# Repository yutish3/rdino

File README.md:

# Rdino - 2040
rp-2040 development board in the shape of arduino uno r3 so it supports its hats and also has esp32 for wifi and bluetooth and 5x5 grid of neo pixel leds

## VISION
main goals I had was making it is that I wanted to have a powerful board on which Arduino hats can fit with wireless capabilities so I used both rp 2040 and esp 32 and connected gpios of both so rp 2040 can off load some tasks to esp 32. so in a sense it is like Arduino UNO but on steroids 

and for usage too it can be used like a normal Arduino UNO 

it has dual microcontroller so all the less important repetative tasks can be off loaded to esp32 and main work can be done by the rp 2040 chip with extra 16M bit memory
and it can be used foor any project like lfr robot , micromouse , rc car etc

## what makes it special (main components)
&#9679; RP2040 :- main microcontroller

&#9679; W25Q128JVS :- 128Mbit Flash Memory for extra juice

&#9679; ESP32-C3-WROOM-02 :- backup microcontroller with wifi and Bluetooth capabilities 

&#9679; 25 X WS2812B-2020 :- programmable rgb leds

## Images

| Component | Purpose | Qty | Cost (INR) | Distributor |
| --- | --- | --- | --- | --- |
| RP2040 (QFN-56) | Main Microcontroller | 1 | ₹81.00 | [Evelta](https://evelta.com/rp2040-264kb-sram-dual-arm-cortex-m0-processor-mcu-by-raspberry-pi/?srsltid=AfmBOopaIG6fpnSNGs3z4S0e6P0bgP9_VYOyHm1yW1iu5uU8jt_uu5J_) |
| ESP32-C3-WROOM-02 | Wi-Fi / BLE Module | 1 | ₹312 | [Evelta](https://evelta.com/esp32-c3-wroom-02-n4-wi-fi-ble-module-4mb-flash-pcb-antenna/?sku=136-ESP32-C3-WROOM-02-N4&utm_source=google&utm_campaign=19958243666&utm_medium=cpc&utm_content=&utm_term=&gad_source=1&gad_campaignid=19958265965&gclid=Cj0KCQjwsMLSBhD9ARIsAIpUTDqEPgMN1OtKYFDDmMqUSGKSXAjHzA4DRwzgzZp3zSiW1o8-RgKeGbgaAoSMEALw_wcB) |
| W25Q128JVS (SOIC-8) | 128Mbit Flash Memory | 1 | ₹223 | [Evelta](https://evelta.com/serial-nor-flash-memory-128mbit-8pin-soic/?sku=153-W25Q128JVSIQ&utm_source=google&utm_campaign=19958243666&utm_medium=cpc&utm_content=&utm_term=&gad_source=1&gad_campaignid=19958265965&gclid=Cj0KCQjwsMLSBhD9ARIsAIpUTDqgAe2PFV_ZbwzCVTig-jSF6n-lNv5TzVO5kI0fkOoLNDz-UcC87KoaAvCyEALw_wcB) |
| AP2112K-3.3 (SOT-23-5) | 3.3V LDO Voltage Regulator | 1 | ₹24 | [Evelta](https://evelta.com/linear-voltage-regulator-positive-fixed-1-output-300ma-ic-sot-23-5/?sku=035-TLV74033PDBVR&utm_source=google&utm_campaign=19958243666&utm_medium=cpc&utm_content=&utm_term=&gad_source=1&gad_campaignid=19958265965&gclid=Cj0KCQjwsMLSBhD9ARIsAIpUTDpVNRkkdR8DkeeqQDI-B0SV4mmE5r7KHuDlczT8pWqQnIAxcDNvTTQaAnOdEALw_wcB#productDescription) |
| WS2812B-2020 (PLCC4) | Addressable RGB LEDs (D1-D24, D27, D29, D31) | 25 | ₹275 | [Robu](https://robu.in/product/1-month-warranty-953/?gad_source=1&gad_campaignid=17427802703&gclid=Cj0KCQjwsMLSBhD9ARIsAIpUTDpt1pzF430Rd8rggMbqOhyDVxqaDctheh1CFh1cCbUzKa_cTqI4nuYaAhGvEALw_wcB) |
| 74AHCT125 | 3.3v to 5v converter | 1 | ₹113 | [Lioncircuit](https://www.lioncircuits.com/parts/74AHCT125PW%2C118) |
| Standard LED (0603) | Status Indicator (D26) | 1 | ₹3.3 | [evelta](https://evelta.com/0603-orange-chip-led/?srsltid=AfmBOopJK48IT0WFYCzFETDcCPIIkiPRop17X2j5vajIVfQTBZ31vxPa) |
| USB-C Receptacle 14-Pin | Power and Data Interface (J1) | 1 | ₹8 | [Hubtronics](https://hubtronics.in/usb-type-c-16p-female-connector-surface-mount?srsltid=AfmBOordf7MpBH0Qx-t9NQyY5B-fdjtzOuCBNZ2MHx8Cz8tkCzKM3Jp4zG4) |
| 1x04 Pin Header/Socket | I/O Expansion / Programming (J6) | 1 | ₹11 | [Robu](https://robu.in/product/fh2-0-09-04pzd-xunpu-plugin1x4-pin-2mm-female-headers-rohs/?gad_source=1&gad_campaignid=17427802703&gclid=CjwKCAjw08fSBhA7EiwAfbQTsMGuGFKjKxeAs85tsGpJZ_VgBg9C0syUiuKSdEVnRGq6vaZT8pyhIhoCEKcQAvD_BwE)|
| 1x06 Pin Header/Socket | I/O Expansion (J2) | 5 | ₹53 | [Robu](https://robu.in/product/6-pin-female-11mm-tall-stackable-header-connector-for-arduino-5pcs/) |
| 1x08 Pin Header/Socket | I/O Expansion (J4, J5) | 2 | ₹32 | [Robu](https://robu.in/product/fh1-27-01-08pzd-xunpu-plugin1x8-pin-1-27mm-female-headers-rohs/?gad_source=1&gad_campaignid=17427802703&gclid=CjwKCAjw08fSBhA7EiwAfbQTsAXYrqE1Rld57TzQKy9yslqVRvfkEbmGVCeCCZim9T4gCUaC_6xX4xoCpCAQAvD_BwE) |
| 1x10 Pin Header/Socket | I/O Expansion (J3) | 1 | ₹17 | [Robu](https://robu.in/product/fh1-27-01-10pzd-xunpu-plugin1x10-pin-1-27mm-female-headers-rohs/) |
| Push Button (KMR2) | Reset / User Input (SW1, SW2) | 2 | ₹126 | [Robu](https://robu.in/product/kmr221nglfs-ck-2-8mm-0-5mm-round-button-50ma-vertical-welding-4-2mm-spst-2n-32v-smd-tactile-switches-rohs/) |
| 1.1kΩ Resistor (0603) | Current Limiting / Pull-up | 1 | ₹1 | [Robu](https://robu.in/product/0603waj0112t5e-uniohm-royal-ohm-100mw-thick-film-resistors-75v-%C2%B1100ppm-%E2%84%83%C2%B15-1-1k%CF%89-0603-chip-resistor-surface-mount-rohs/) |
| 4.7kΩ Resistor (0603) | I2C / General Pull-up | 2 | ₹5 | [Robu](https://robu.in/product/rt0603brd074k7l-yageo-res-thin-film-0603-4-7k-ohm-0-1-0-1w1-10w-%C2%B125ppm-c-pad-smd-t-r/) |
| 10kΩ Resistor (0603) | Pull-up / Pull-down | 3 | ₹3 | [Robu](https://robu.in/product/10k-ohm-1-4w-0603-surface-mount-chip-resistor-pack-of-100/) |
| 5.1kΩ Resistor (0603) | USB-C CC line Pull-down | 2 | ₹3 | [Robu](https://robu.in/product/rt0603fre075k1l-yageo-100mw-thin-film-resistor-75v-%C2%B150ppm-%E2%84%83-%C2%B11-5-1k%CF%89-0603-chip-resistor-surface-mount-rohs/) |
| 1μF Capacitor (0603) | Decoupling / Bypass | 6 | ₹8.5 | [Robu](https://robu.in/product/1uf-1000nf-50v-capacitor-0603-smd-package-pack-of-20/) |
| 10pF Capacitor (0603) | Crystal Load Capacitors | 2 | ₹1 | [Robu](https://robu.in/product/10pf-0603-surface-mount-multilayer-ceramic-capacitor-pack-of-50/) |
| Crystal 3225 (4-Pin) | Clock Source for RP2040 (Y1) | 1 | ₹101 | [lion circuit](https://www.lioncircuits.com/parts/NX3225SA-12MHZ-STD-CSR-6) |
| PCB | PCB | 1 | ₹3375 | [Robu] |
| Hot plate | soldering | 1 | ₹2,749 | [Amazon](https://www.amazon.in/Preheating-Soldering-Preheater-Platform-56x56x35mm/dp/B0C7W3W8C4?source=ps-sl-shoppingads-lpcontext&psc=1&smid=A2PRL1RFFZO5CK) |
| soldering flux | gooye paste to combine components | 1 | ₹400 | [amazon](https://www.amazon.in/Electron-Soldering-Syringe-No-Clean-Electronics/dp/B0GTMJHBJ4) |

The Bare Components : ₹1,708.80

PCB Fabrication (Robu): ₹3,375.00

Assembly Tools (Amazon): ₹3,262.00

Grand Total: ₹8,345.8

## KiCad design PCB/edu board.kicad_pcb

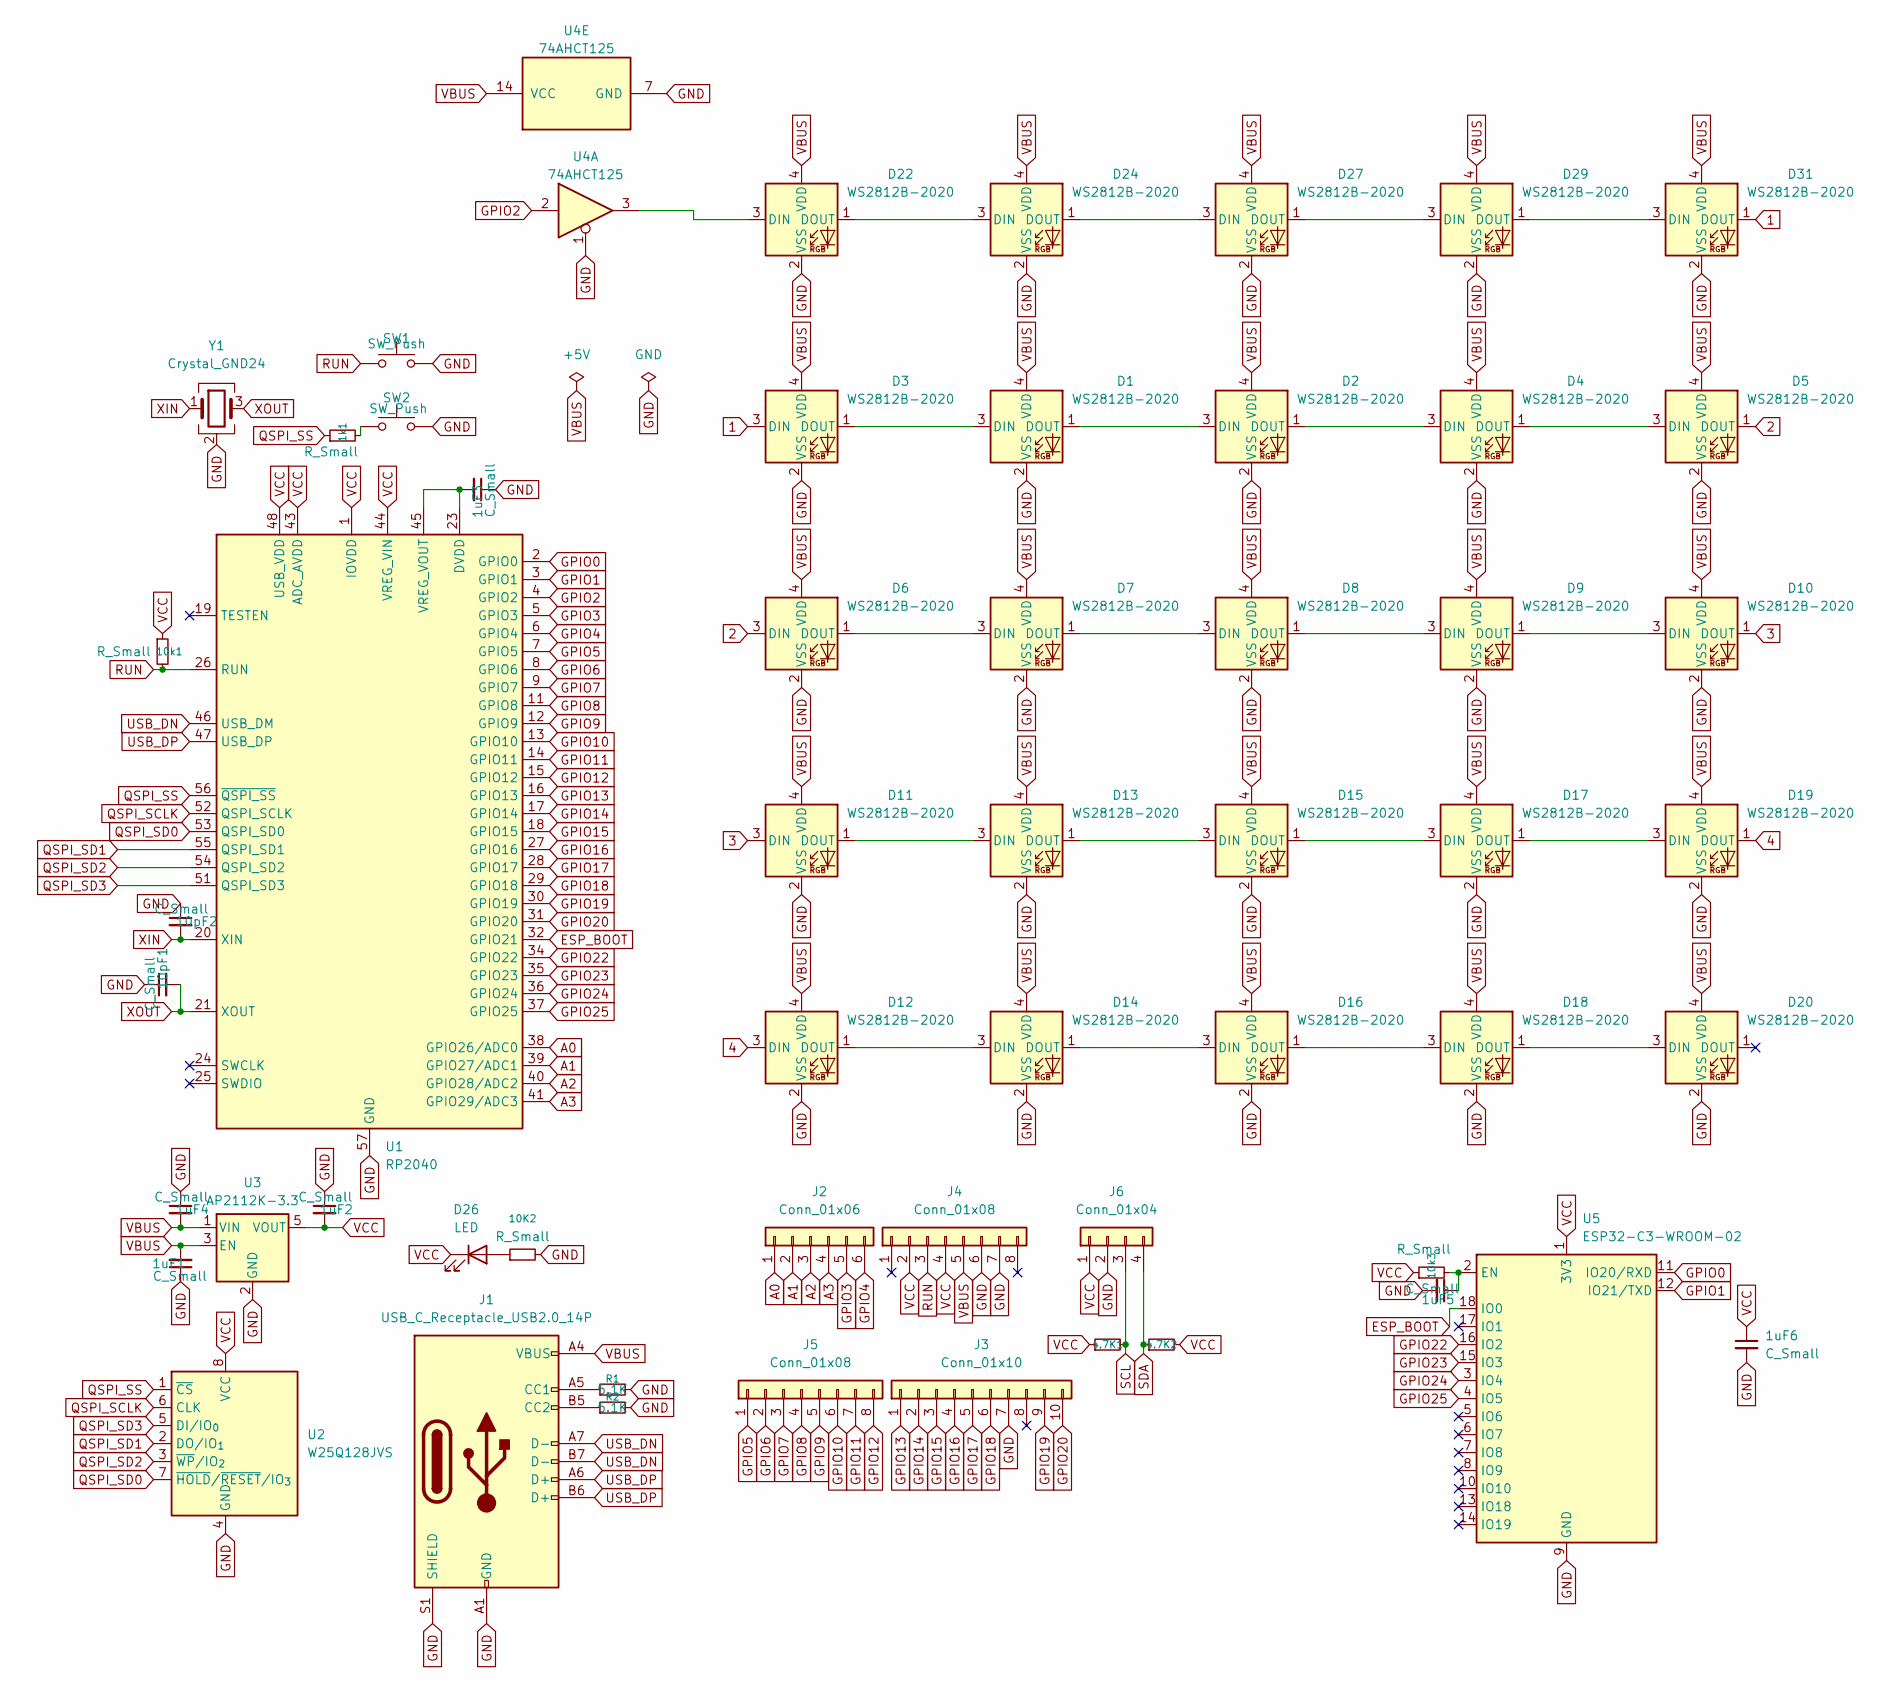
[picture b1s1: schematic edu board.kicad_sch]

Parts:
1k1, 4.7K1, 4.7K2, 10K2, 10k1, 10k3: R_Small; R_0603_1608Metric
1uF1, 1uF2, 1uF3, 1uF4, 1uF5, 1uF6, 10pF1, 10pF2: C_Small; C_0603_1608Metric
D1, D2, D3, D4, D5, D6, D7, D8, D9, D10, D11, D12, D13, D14, D15, D16, D17, D18, D19, D20, D22, D24, D27, D29, D31: WS2812B-2020; LED_WS2812B-2020_PLCC4_2.0x2.0mm
D26: LED; LED_0603_1608Metric
J1: USB_C_Receptacle_USB2.0_14P; USB_C_Receptacle_HRO_TYPE-C-31-M-12
J2: Conn_01x06; PinSocket_1x06_P2.54mm_Vertical
J3: Conn_01x10; PinSocket_1x10_P2.54mm_Vertical
J4, J5: Conn_01x08; PinSocket_1x08_P2.54mm_Vertical
J6: Conn_01x04; PinHeader_1x04_P2.54mm_Vertical
R1, R2: 5.1K; R_0603_1608Metric
SW1, SW2: SW_Push; SW_Push_1P1T_NO_CK_KMR2
U1: RP2040; QFN-56-1EP_7x7mm_P0.4mm_EP3.2x3.2mm
U2: W25Q128JVS; SOIC-8_5.3x5.3mm_P1.27mm
U3: AP2112K-3.3; SOT-23-5
U4: 74AHCT125; TSSOP-14_4.4x5mm_P0.65mm
U5: ESP32-C3-WROOM-02
Y1: Crystal_GND24; Crystal_SMD_3225-4Pin_3.2x2.5mm

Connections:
1: D3.3 (DIN), D31.1 (DOUT)
2: D5.1 (DOUT), D6.3 (DIN)
3: D10.1 (DOUT), D11.3 (DIN)
4: D12.3 (DIN), D19.1 (DOUT)
A0: J2.1, U1.38 (GPIO26/ADC0)
A1: J2.2, U1.39 (GPIO27/ADC1)
A2: J2.3, U1.40 (GPIO28/ADC2)
A3: J2.4, U1.41 (GPIO29/ADC3)
ESP_BOOT: U1.32 (GPIO21), U5.18 (IO0)
GND: 1uF1.1, 1uF2.1, 1uF3.1, 1uF4.1, 1uF5.2, 1uF6.2, 10K2.2, 10pF1.1, 10pF2.1, D1.2 (VSS), D2.2 (VSS), D3.2 (VSS), D4.2 (VSS), D5.2 (VSS), D6.2 (VSS), D7.2 (VSS), D8.2 (VSS), D9.2 (VSS), D10.2 (VSS), D11.2 (VSS), D12.2 (VSS), D13.2 (VSS), D14.2 (VSS), D15.2 (VSS), D16.2 (VSS), D17.2 (VSS), D18.2 (VSS), D19.2 (VSS), D20.2 (VSS), D22.2 (VSS), D24.2 (VSS), D27.2 (VSS), D29.2 (VSS), D31.2 (VSS), J1.A1 (GND), J1.A12 (GND), J1.B1 (GND), J1.B12 (GND), J1.S1 (SHIELD), J3.7, J4.6, J4.7, J6.2, R1.2, R2.2, SW1.2, SW2.2, U1.57 (GND), U2.4 (GND), U3.2 (GND), U4.1, U4.7 (GND), U5.9 (GND), U5.19 (GND), Y1.2 (G), Y1.4 (G)
GPIO0: U1.2 (GPIO0), U5.11 (IO20/RXD)
GPIO1: U1.3 (GPIO1), U5.12 (IO21/TXD)
GPIO2: U1.4 (GPIO2), U4.2
GPIO3: J2.5, U1.5 (GPIO3)
GPIO4: J2.6, U1.6 (GPIO4)
GPIO5: J5.1, U1.7 (GPIO5)
GPIO6: J5.2, U1.8 (GPIO6)
GPIO7: J5.3, U1.9 (GPIO7)
GPIO8: J5.4, U1.11 (GPIO8)
GPIO9: J5.5, U1.12 (GPIO9)
GPIO10: J5.6, U1.13 (GPIO10)
GPIO11: J5.7, U1.14 (GPIO11)
GPIO12: J5.8, U1.15 (GPIO12)
GPIO13: J3.1, U1.16 (GPIO13)
GPIO14: J3.2, U1.17 (GPIO14)
GPIO15: J3.3, U1.18 (GPIO15)
GPIO16: J3.4, U1.27 (GPIO16)
GPIO17: J3.5, U1.28 (GPIO17)
GPIO18: J3.6, U1.29 (GPIO18)
GPIO19: J3.9, U1.30 (GPIO19)
GPIO20: J3.10, U1.31 (GPIO20)
GPIO22: U1.34 (GPIO22), U5.16 (IO2)
GPIO23: U1.35 (GPIO23), U5.15 (IO3)
GPIO24: U1.36 (GPIO24), U5.3 (IO4)
GPIO25: U1.37 (GPIO25), U5.4 (IO5)
unnamed: 1k1.2, SW2.1
unnamed: D1.3 (DIN), D3.1 (DOUT)
unnamed: D1.1 (DOUT), D2.3 (DIN)
unnamed: D2.1 (DOUT), D4.3 (DIN)
unnamed: D4.1 (DOUT), D5.3 (DIN)
unnamed: D6.1 (DOUT), D7.3 (DIN)
unnamed: D7.1 (DOUT), D8.3 (DIN)
unnamed: D8.1 (DOUT), D9.3 (DIN)
unnamed: D9.1 (DOUT), D10.3 (DIN)
unnamed: D11.1 (DOUT), D13.3 (DIN)
unnamed: D12.1 (DOUT), D14.3 (DIN)
unnamed: D13.1 (DOUT), D15.3 (DIN)
unnamed: D14.1 (DOUT), D16.3 (DIN)
unnamed: D15.1 (DOUT), D17.3 (DIN)
unnamed: D16.1 (DOUT), D18.3 (DIN)
unnamed: D17.1 (DOUT), D19.3 (DIN)
unnamed: D18.1 (DOUT), D20.3 (DIN)
unnamed: D22.3 (DIN), U4.3
unnamed: D22.1 (DOUT), D24.3 (DIN)
unnamed: D24.1 (DOUT), D27.3 (DIN)
unnamed: 10K2.1, D26.2 (A)
unnamed: D27.1 (DOUT), D29.3 (DIN)
unnamed: D29.1 (DOUT), D31.3 (DIN)
unnamed: J1.A5 (CC1), R1.1
unnamed: J1.B5 (CC2), R2.1
unnamed: 1uF3.2, U1.23 (DVDD), U1.45 (VREG_VOUT), U1.50 (DVDD)
unnamed: 1uF5.1, 10k3.2, U5.2 (EN)
QSPI_SCLK: U1.52 (QSPI_SCLK), U2.6 (CLK)
QSPI_SD0: U1.53 (QSPI_SD0), U2.7 (~HOLD/~RESET/IO_{3})
QSPI_SD1: U1.55 (QSPI_SD1), U2.2 (DO/IO_{1})
QSPI_SD2: U1.54 (QSPI_SD2), U2.3 (~WP/IO_{2})
QSPI_SD3: U1.51 (QSPI_SD3), U2.5 (DI/IO_{0})
QSPI_SS: 1k1.1, U1.56 (~QSPI_SS), U2.1 (~CS)
RUN: 10k1.2, J4.3, SW1.1, U1.26 (RUN)
SCL: 4.7K1.2, J6.3
SDA: 4.7K2.1, J6.4
USB_DN: J1.A7 (D-), J1.B7 (D-), U1.46 (USB_DM)
USB_DP: J1.A6 (D+), J1.B6 (D+), U1.47 (USB_DP)
VBUS: 1uF1.2, 1uF4.2, D1.4 (VDD), D2.4 (VDD), D3.4 (VDD), D4.4 (VDD), D5.4 (VDD), D6.4 (VDD), D7.4 (VDD), D8.4 (VDD), D9.4 (VDD), D10.4 (VDD), D11.4 (VDD), D12.4 (VDD), D13.4 (VDD), D14.4 (VDD), D15.4 (VDD), D16.4 (VDD), D17.4 (VDD), D18.4 (VDD), D19.4 (VDD), D20.4 (VDD), D22.4 (VDD), D24.4 (VDD), D27.4 (VDD), D29.4 (VDD), D31.4 (VDD), J1.A4 (VBUS), J1.A9 (VBUS), J1.B4 (VBUS), J1.B9 (VBUS), J4.5, U3.1 (VIN), U3.3 (EN), U4.14 (VCC)
VCC: 1uF2.2, 1uF6.1, 4.7K1.1, 4.7K2.2, 10k1.1, 10k3.1, D26.1 (K), J4.2, J4.4, J6.1, U1.1 (IOVDD), U1.10 (IOVDD), U1.22 (IOVDD), U1.33 (IOVDD), U1.42 (IOVDD), U1.43 (ADC_AVDD), U1.44 (VREG_VIN), U1.48 (USB_VDD), U1.49 (IOVDD), U2.8 (VCC), U3.5 (VOUT), U5.1 (3V3)
XIN: 10pF2.2, U1.20 (XIN), Y1.1
XOUT: 10pF1.2, U1.21 (XOUT), Y1.3

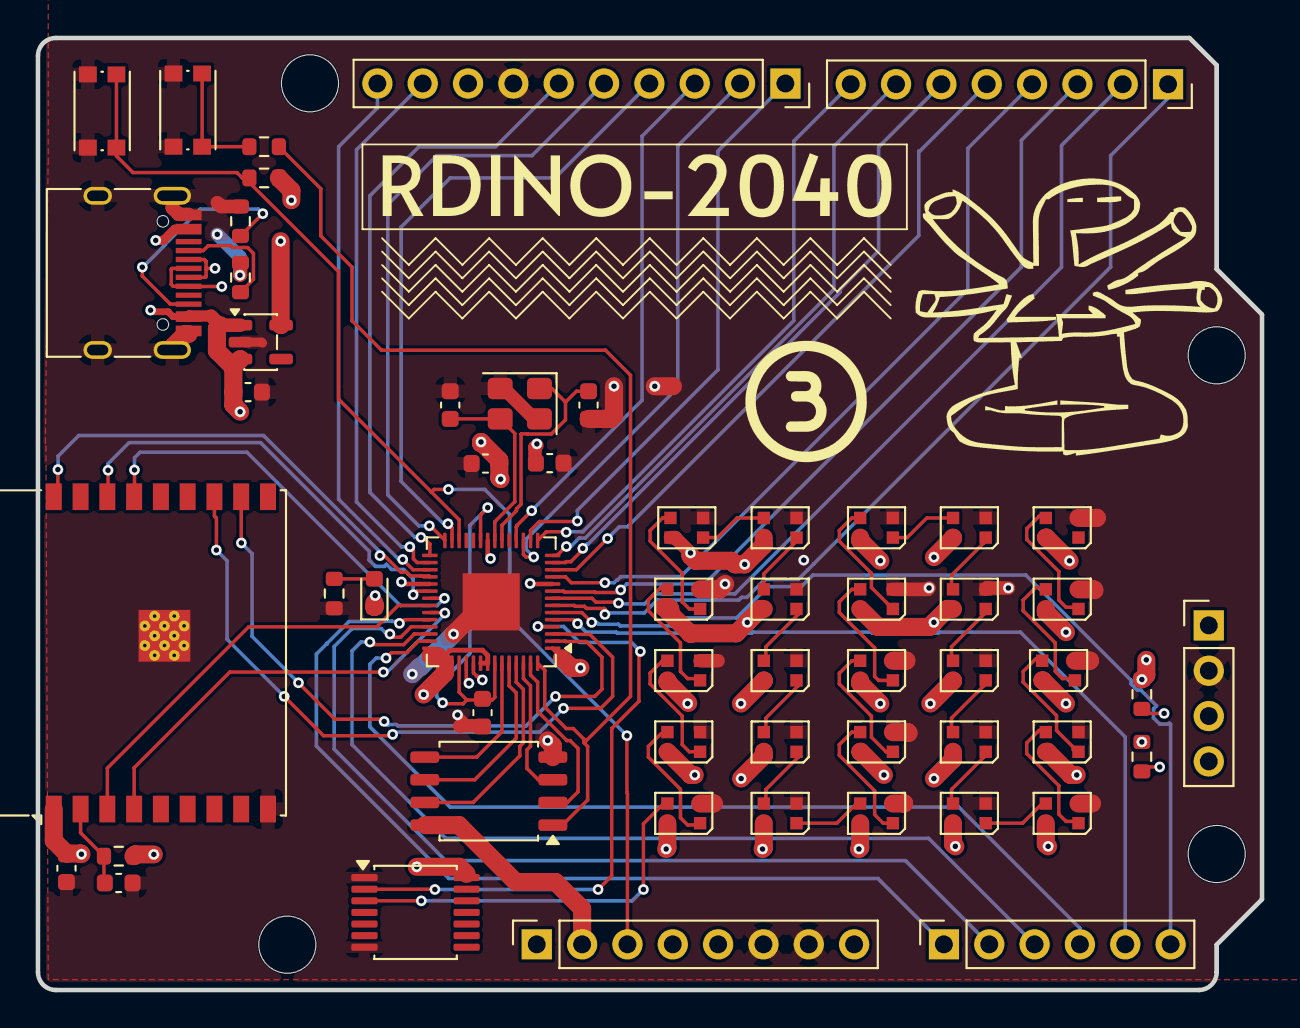
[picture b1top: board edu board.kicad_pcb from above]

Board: 4 copper layers, 68.6 x 53.3 mm, 56 parts (0 on the bottom side), 77 nets.

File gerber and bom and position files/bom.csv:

Designator,Footprint,Quantity,Value,LCSC Part #
"10K1, 10K2, 10K3, 1K1, 4.7K1, 4.7K2",0603,6,R_Small,
"1UF1, 1UF2, 1UF3, 1UF4, 1UF5, 1UF6, 27PF1, 27PF2",0603,8,C_Small,
"D1, D10, D11, D12, D13, D14, D15, D16, D17, D18, D19, D2, D20, D22, D24, D27, D29, D3, D31, D4, D5, D6, D7, D8, D9",LED_WS2812B-2020_PLCC4_2.0x2.0mm,25,WS2812B-2020,
D26,0603,1,LED,
J1,USB_C_Receptacle_HRO_TYPE-C-31-M-12,1,USB_C_Receptacle_USB2.0_14P,
J2,PinSocket_1x06_P2.54mm_Vertical,1,Conn_01x06,
J3,PinSocket_1x10_P2.54mm_Vertical,1,Conn_01x10,
"J4, J5",PinSocket_1x08_P2.54mm_Vertical,2,Conn_01x08,
J6,PinHeader_1x04_P2.54mm_Vertical,1,Conn_01x04,
"R1, R2",0603,2,5.1K,
"SW1, SW2",SW_Push_1P1T_NO_CK_KMR2,2,SW_Push,
U1,QFN-56-1EP_7x7mm_P0.4mm_EP3.2x3.2mm,1,RP2040,
U2,SOIC-8_5.3x5.3mm_P1.27mm,1,W25Q128JVS,
U3,SOT-23-5,1,AP2112K-3.3,
U5,ESP32-C3-WROOM-02,1,ESP32-C3-WROOM-02,
Y1,Crystal_SMD_3225-4Pin_3.2x2.5mm,1,Crystal_GND24,
